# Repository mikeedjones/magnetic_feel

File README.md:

# magnetic_feel

Though magnetic fields are ubiquitous in the world today, humans have no innate way of sensing them. The intangibility of magnetic fields makes them that much harder to understand. The Magnetic-Feel is an extrasensory toy designed to help students better understand magnetic fields.

The principle of the toy is simple - it's a 2 cm x 2 cm cube which vibrates in the presence of a magnetic field.  As the strength of the vibrations is proportional to the strength of the field,  moving the toy around in a magnetic field allows the student to build up a 3D-mental map of the field, which helps the student understand the 3D-structure of the field.

The housing for the toy was designed in Fusion360 and then 3D printed. The design can be downloaded [here](http://a360.co/2m23xQc).

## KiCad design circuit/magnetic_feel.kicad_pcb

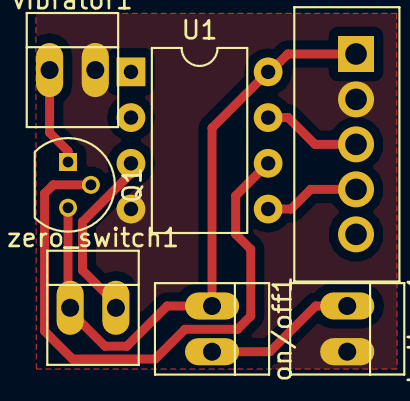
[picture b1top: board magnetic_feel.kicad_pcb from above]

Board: 2 copper layers, 7 parts (0 on the bottom side), 8 nets.

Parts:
J1: CONN_01X05; Wafer_Vertical15x5.8x7RM2.5-5
Q1: PN2222A; TO-92_Molded_Narrow
U1: ATTINY10-P; DIP-8_W7.62mm
battery1: CONN_01X02; PINHEAD1-2
on/off1: CONN_01X02; PINHEAD1-2
vibrator1: CONN_01X02; PINHEAD1-2
zero_switch1: CONN_01X02; PINHEAD1-2

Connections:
unnamed: J1.1, Q1.3, U1.8, on/off1.1, zero_switch1.1
unnamed: J1.2, U1.4, battery1.2, vibrator1.2
unnamed: J1.3, U1.7
unnamed: J1.4, U1.5
unnamed: Q1.1, vibrator1.1
unnamed: Q1.2, U1.6
unnamed: U1.3, zero_switch1.2
unnamed: battery1.1, on/off1.2

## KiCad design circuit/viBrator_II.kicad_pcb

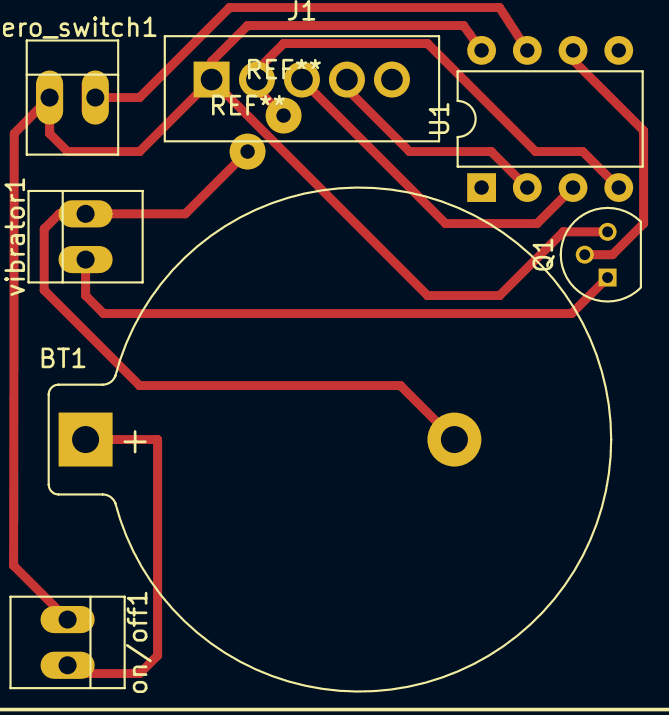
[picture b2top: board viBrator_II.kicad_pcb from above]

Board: 2 copper layers, 7 parts (0 on the bottom side), 8 nets.

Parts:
BT1: Battery; Keystone_106_1x20mm-CoinCell
J1: CONN_01X05; Wafer_Vertical15x5.8x7RM2.5-5
Q1: PN2222A; TO-92_Molded_Narrow
U1: ATTINY10-P; DIP-8_W7.62mm
on/off1: CONN_01X02; PINHEAD1-2
vibrator1: CONN_01X02; PINHEAD1-2
zero_switch1: CONN_01X02; PINHEAD1-2

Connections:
unnamed: BT1.1, on/off1.2
unnamed: BT1.2, J1.2, U1.4, vibrator1.2
unnamed: J1.1, Q1.3, U1.8, on/off1.1, zero_switch1.1
unnamed: J1.3, U1.3
unnamed: J1.4, U1.2
unnamed: Q1.1, vibrator1.1
unnamed: Q1.2, U1.6
unnamed: U1.7, zero_switch1.2

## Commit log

2019-03-08 extrasensory toy to teach students about magnetic fields
2019-03-08 renamed project
    renamed project files
